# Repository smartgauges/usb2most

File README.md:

# usb2most
USB to MOST adapter to translate audio from a USB([UAC1](https://en.wikipedia.org/wiki/USB#Audio_streaming)) to MOST([Media Oriented Systems Transport](https://en.wikipedia.org/wiki/MOST_Bus)) bus

Interfaces:
- 8 audio channels(16bit/48kHz) over MOST bus
- 2 audio channels(16bit/48kHz) over USB
- 4 CAN for HS/HS" and MS/MS"
- 1 LIN for analogue watch
- 1 UART for CANBUS emulation

[More info](https://www.drive2.ru/l/524415370476389031/)

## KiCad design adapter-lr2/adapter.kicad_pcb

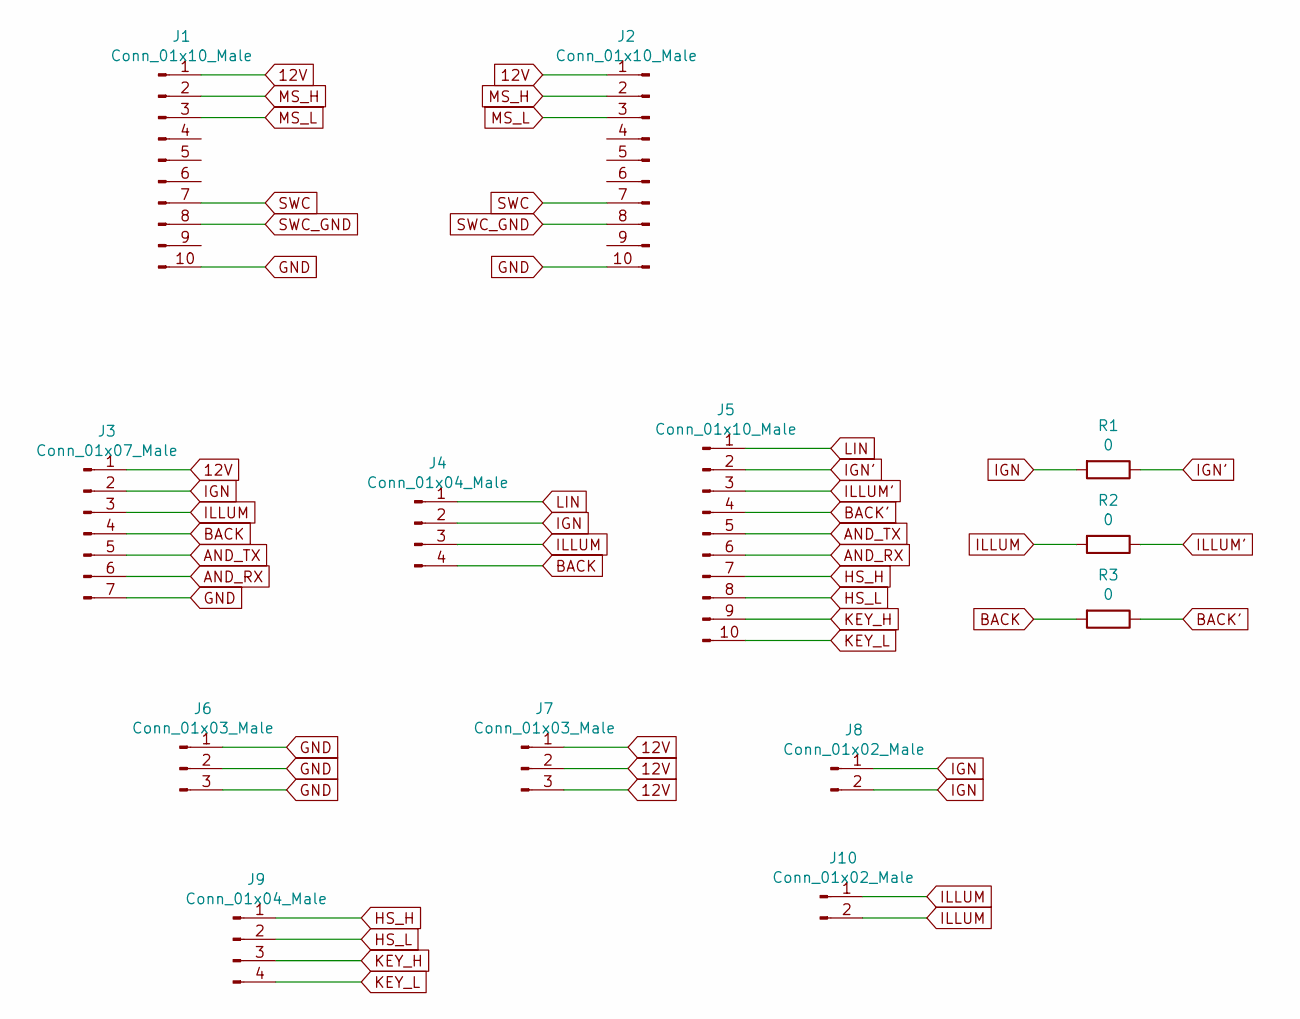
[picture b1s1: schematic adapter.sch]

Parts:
J1: Conn_01x10_Male; IL-AG5-10P-S3L2
J2, J5: Conn_01x10_Male; PinHeader_1x10_P2.54mm_Vertical
J3: Conn_01x07_Male; PinHeader_1x07_P2.54mm_Vertical
J4, J9: Conn_01x04_Male; PinHeader_1x04_P2.54mm_Vertical
J6, J7: Conn_01x03_Male; PinHeader_1x03_P2.54mm_Vertical
J8, J10: Conn_01x02_Male; PinHeader_1x02_P2.54mm_Vertical
R1, R2, R3: 0; R_0805_2012Metric

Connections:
12V: J1.1, J2.1, J3.1, J7.1, J7.2, J7.3
AND_RX: J3.6, J5.6
AND_TX: J3.5, J5.5
BACK: J3.4, J4.4, R3.2
BACK': J5.4, R3.1
GND: J1.10, J2.10, J3.7, J6.1, J6.2, J6.3
HS_H: J5.7, J9.1
HS_L: J5.8, J9.2
IGN: J3.2, J4.2, J8.1, J8.2, R1.2
IGN': J5.2, R1.1
ILLUM: J3.3, J4.3, J10.1, J10.2, R2.2
ILLUM': J5.3, R2.1
KEY_H: J5.9, J9.3
KEY_L: J5.10, J9.4
LIN: J4.1, J5.1
MS_H: J1.2, J2.2
MS_L: J1.3, J2.3
SWC: J1.7, J2.7
SWC_GND: J1.8, J2.8

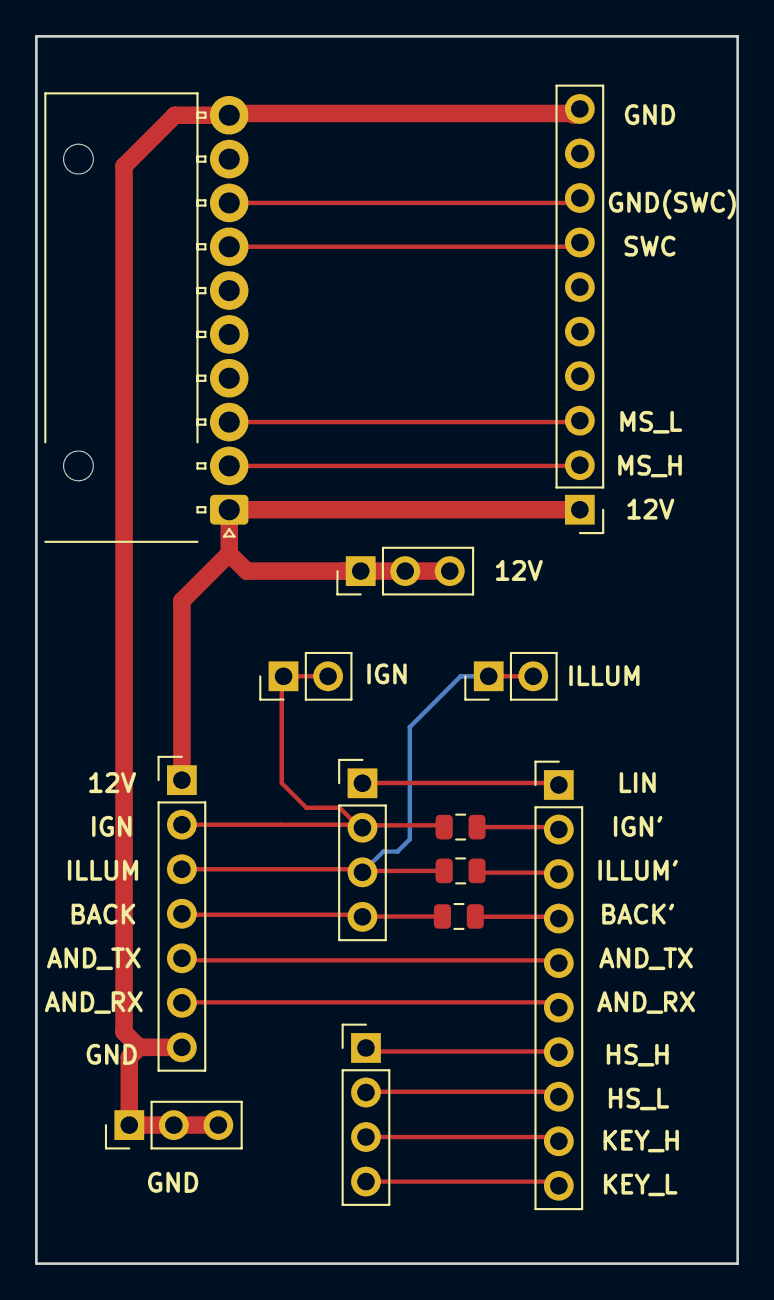
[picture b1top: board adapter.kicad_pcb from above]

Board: 2 copper layers, 40.0 x 70.0 mm, 13 parts (0 on the bottom side), 19 nets.

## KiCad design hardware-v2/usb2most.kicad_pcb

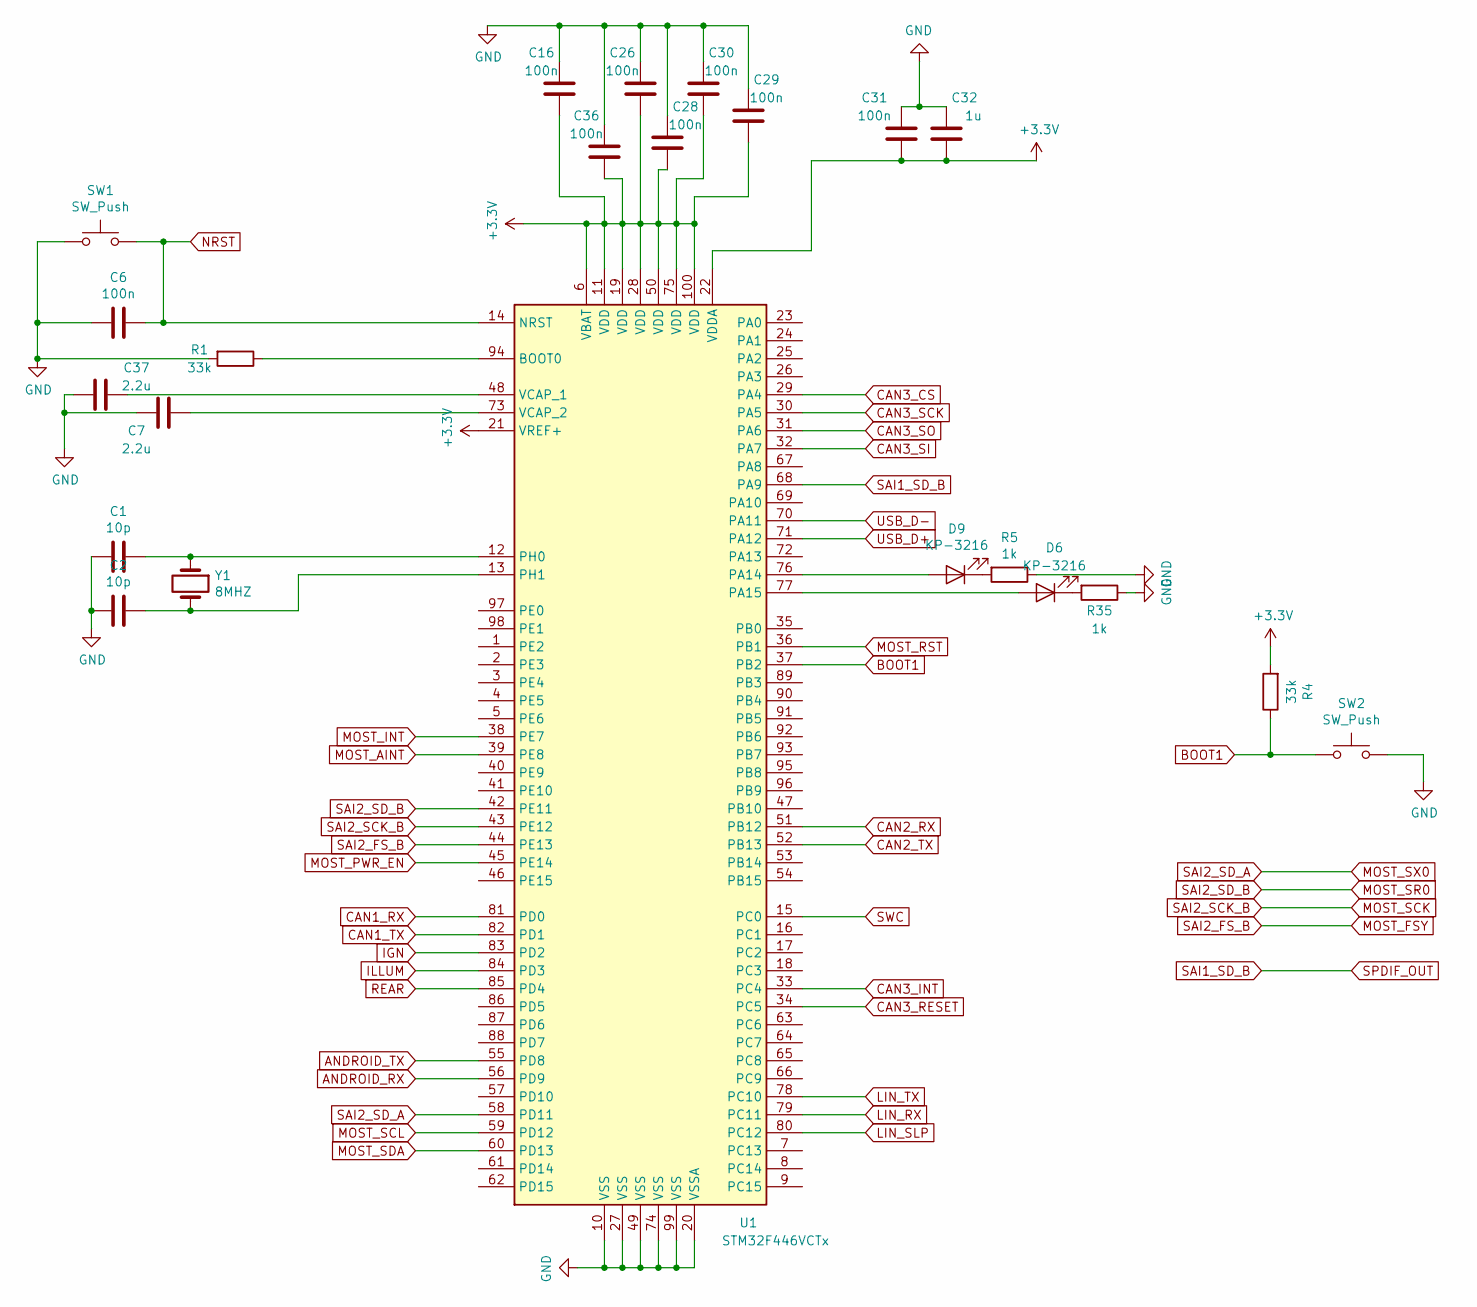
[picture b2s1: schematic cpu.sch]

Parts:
C1, C2: 10p; C_0805_2012Metric
C6, C16, C26, C28, C29, C30, C31, C36: 100n; C_0805_2012Metric
C7, C37: 2.2u; C_1206_3216Metric
C32: 1u; C_1206_3216Metric
D6, D9: KP-3216; R_1206_3216Metric
R1, R4: 33k; R_0805_2012Metric
R5, R35: 1k; R_0805_2012Metric
SW1, SW2: SW_Push; SW_SPST_EVQPE1
U1: STM32F446VCTx; LQFP-100_14x14mm_P0.5mm
Y1: 8MHZ; Crystal_HC49-U_Vertical

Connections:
+3V3: C16.1, C26.1, C28.1, C29.1, C30.1, C31.1, C32.1, C36.1, R4.2, U1.6 (VBAT), U1.11 (VDD), U1.19 (VDD), U1.21 (VREF+), U1.22 (VDDA), U1.28 (VDD), U1.50 (VDD), U1.75 (VDD), U1.100 (VDD); also elsewhere on the board
ANDROID_RX: U1.56 (PD9); also elsewhere on the board
ANDROID_TX: U1.55 (PD8); also elsewhere on the board
BOOT1: R4.1, SW2.1, U1.37 (PB2)
CAN1_RX: U1.81 (PD0); also elsewhere on the board
CAN1_TX: U1.82 (PD1); also elsewhere on the board
CAN2_RX: U1.51 (PB12); also elsewhere on the board
CAN2_TX: U1.52 (PB13); also elsewhere on the board
CAN3_CS: U1.29 (PA4); also elsewhere on the board
CAN3_INT: U1.33 (PC4); also elsewhere on the board
CAN3_RESET: U1.34 (PC5); also elsewhere on the board
CAN3_SCK: U1.30 (PA5); also elsewhere on the board
CAN3_SI: U1.32 (PA7); also elsewhere on the board
CAN3_SO: U1.31 (PA6); also elsewhere on the board
GND: C1.2, C2.2, C6.2, C7.2, C16.2, C26.2, C28.2, C29.2, C30.2, C31.2, C32.2, C36.2, C37.2, R1.2, R5.1, R35.1, SW1.1, SW2.2, U1.10 (VSS), U1.20 (VSSA), U1.27 (VSS), U1.49 (VSS), U1.74 (VSS), U1.99 (VSS); also elsewhere on the board
IGN: U1.83 (PD2); also elsewhere on the board
ILLUM: U1.84 (PD3); also elsewhere on the board
LIN_RX: U1.79 (PC11); also elsewhere on the board
LIN_SLP: U1.80 (PC12); also elsewhere on the board
LIN_TX: U1.78 (PC10); also elsewhere on the board
MOST_AINT: U1.39 (PE8); also elsewhere on the board
MOST_FSY: U1.44 (PE13); also elsewhere on the board
MOST_INT: U1.38 (PE7); also elsewhere on the board
MOST_PWR_EN: U1.45 (PE14); also elsewhere on the board
MOST_RST: U1.36 (PB1); also elsewhere on the board
MOST_SCK: U1.43 (PE12); also elsewhere on the board
MOST_SCL: U1.59 (PD12); also elsewhere on the board
MOST_SDA: U1.60 (PD13); also elsewhere on the board
MOST_SR0: U1.42 (PE11); also elsewhere on the board
MOST_SX0: U1.58 (PD11); also elsewhere on the board
NRST: C6.1, SW1.2, U1.14 (NRST)
unnamed: C1.1, U1.12 (PH0), Y1.1
unnamed: C2.1, U1.13 (PH1), Y1.2
unnamed: C7.1, U1.73 (VCAP_2)
unnamed: C37.1, U1.48 (VCAP_1)
unnamed: D6.1 (K), R35.2
unnamed: D6.2 (A), U1.77 (PA15)
unnamed: D9.1 (K), R5.2
unnamed: D9.2 (A), U1.76 (PA14)
unnamed: R1.1, U1.94 (BOOT0)
REAR: U1.85 (PD4); also elsewhere on the board
SAI1_SD_B: U1.68 (PA9); also elsewhere on the board
SWC: U1.15 (PC0); also elsewhere on the board
USB_D+: U1.71 (PA12); also elsewhere on the board
USB_D-: U1.70 (PA11); also elsewhere on the board

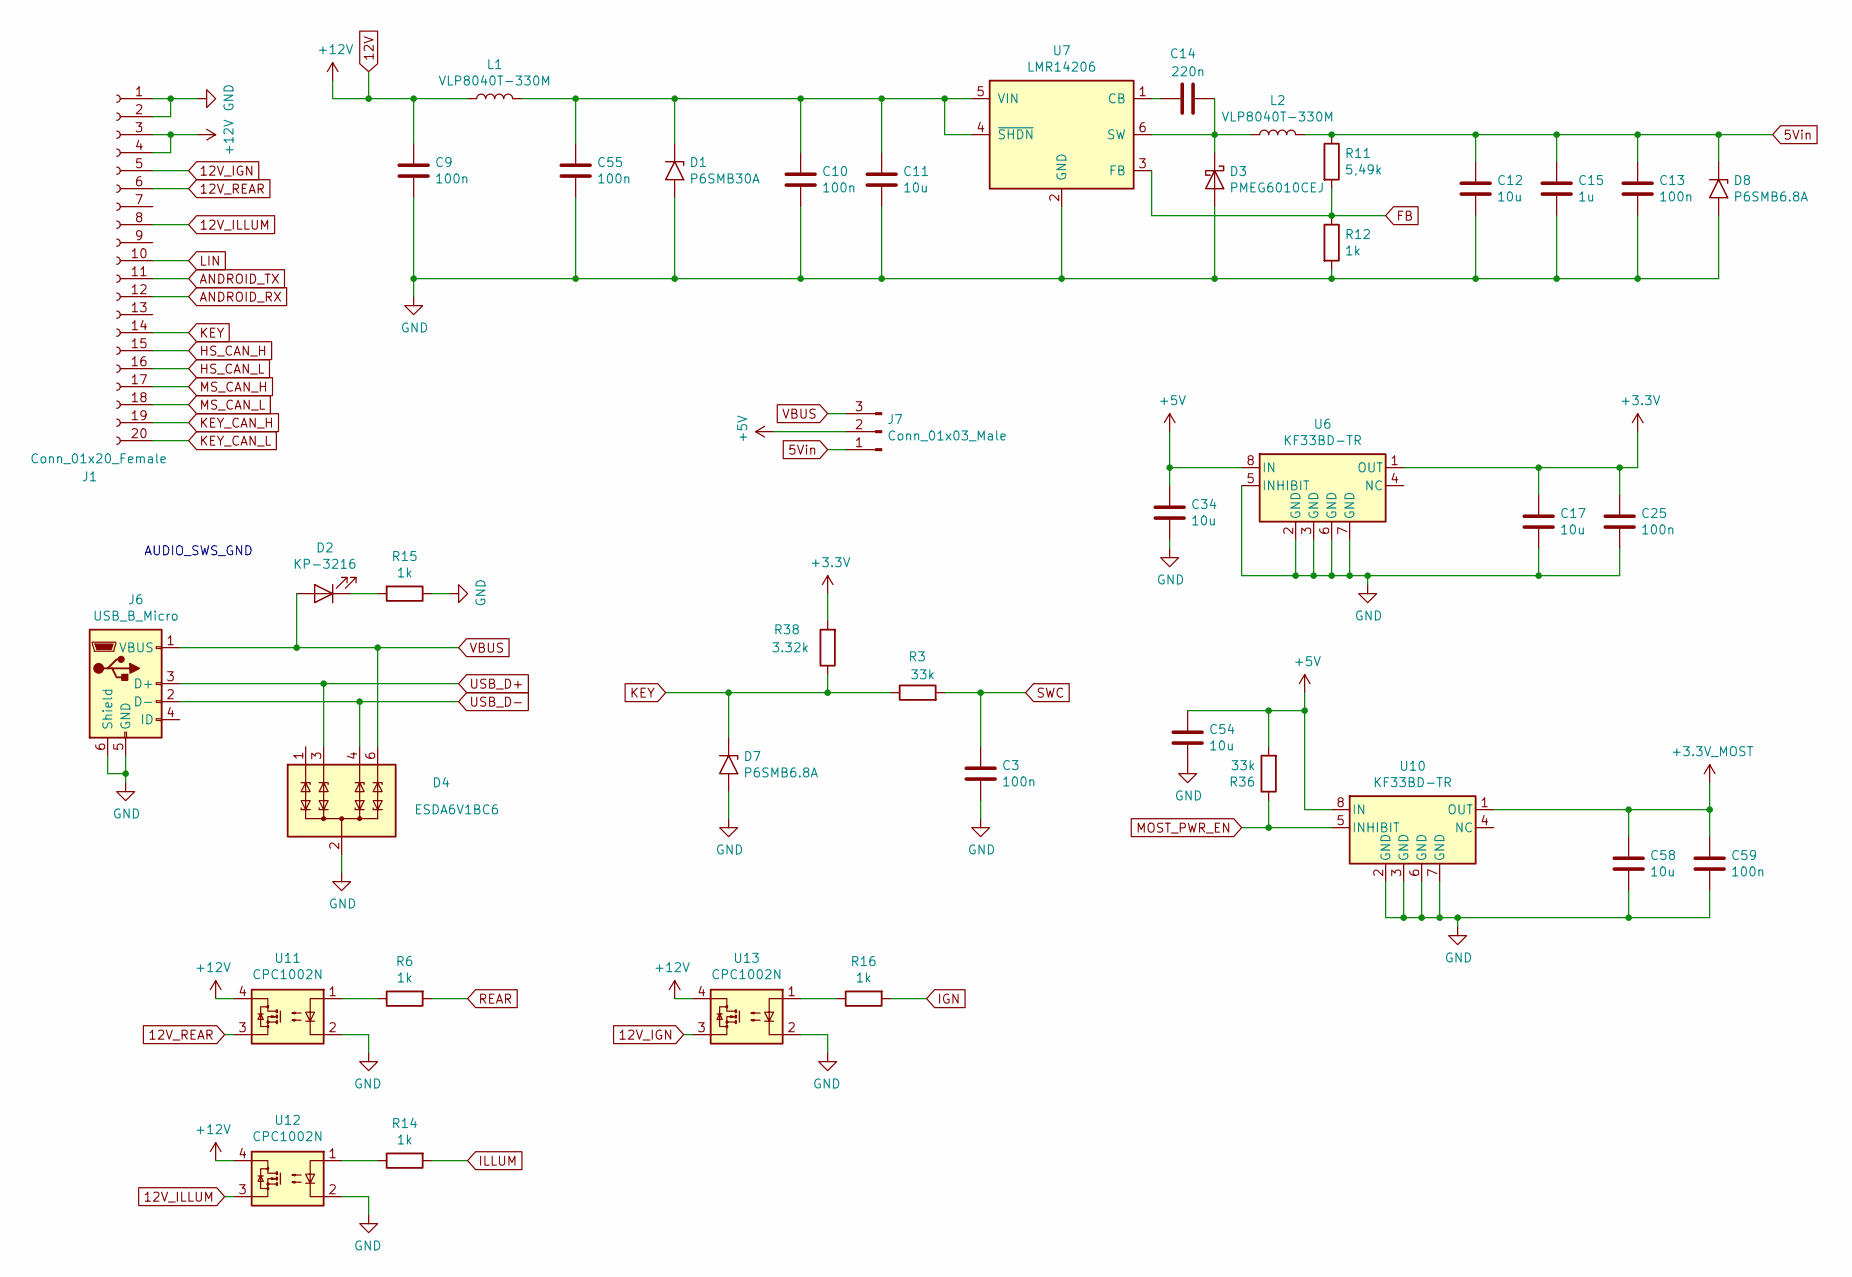
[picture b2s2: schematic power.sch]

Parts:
C3: 100n; C_1206_3216Metric
C9, C10, C13, C25, C55, C59: 100n; C_0805_2012Metric
C11, C12: 10u; C_1812_4532Metric
C14: 220n; C_0805_2012Metric
C15: 1u; C_1206_3216Metric
C17, C34, C54, C58: 10u; C_1206_3216Metric
D1: P6SMB30A; D_SMB
D2: KP-3216; R_1206_3216Metric
D3: PMEG6010CEJ; D_SOD-323
D4: ESDA6V1BC6; SOT-23-6
D7, D8: P6SMB6.8A; D_SMB
J1: Conn_01x20_Female; PinHeader_2x10_P2.00mm_Vertical
J6: USB_B_Micro; USB_Micro-B_Molex-105017-0001
J7: Conn_01x03_Male; PinSocket_1x03_P2.54mm_Vertical
L1, L2: VLP8040T-330M; L_TDK_VLP8040
R3, R36: 33k; R_0805_2012Metric
R6, R12, R14, R15, R16: 1k; R_0805_2012Metric
R11: 5,49k; R_0805_2012Metric
R38: 3.32k; R_0805_2012Metric
U6, U10: KF33BD-TR; SO-8_3.9x4.9mm_P1.27mm
U7: LMR14206; SOT-23-6_Handsoldering
U11, U12, U13: CPC1002N; SOP-4_3.8x4.1mm_P2.54mm

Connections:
5Vin: C12.1, C13.1, C15.1, D8.1 (A1), J7.1, L2.2, R11.1
12V: C9.1, J1.3, J1.4, L1.1, U11.4, U12.4, U13.4; also elsewhere on the board
12V_IGN: J1.5, U13.3
12V_ILLUM: J1.8, U12.3
12V_REAR: J1.6, U11.3
+3.3_MOST: C58.1, C59.1, U10.1 (OUT); also elsewhere on the board
+3V3: C17.1, C25.1, R38.2, U6.1 (OUT); also elsewhere on the board
+5V: C34.1, C54.1, J7.2, R36.2, U6.8 (IN), U10.8 (IN); also elsewhere on the board
ANDROID_RX: J1.12; also elsewhere on the board
ANDROID_TX: J1.11; also elsewhere on the board
FB: R11.2, R12.1, U7.3 (FB)
GND: C3.2, C9.2, C10.2, C11.2, C12.2, C13.2, C15.2, C17.2, C25.2, C34.2, C54.2, C55.2, C58.2, C59.2, D1.2 (A2), D3.2 (A), D4.2 (COM), D4.5 (COM), D7.2 (A2), D8.2 (A2), J1.1, J1.2, J6.5 (GND), J6.6 (Shield), R12.2, R15.1, U6.2 (GND), U6.3 (GND), U6.5 (INHIBIT), U6.6 (GND), U6.7 (GND), U7.2 (GND), U10.2 (GND), U10.3 (GND), U10.6 (GND), U10.7 (GND), U11.2, U12.2, U13.2; also elsewhere on the board
HS_CAN_H: J1.15; also elsewhere on the board
HS_CAN_L: J1.16; also elsewhere on the board
IGN: R16.2; also elsewhere on the board
ILLUM: R14.2; also elsewhere on the board
KEY: D7.1 (A1), J1.14, R3.1, R38.1
KEY_CAN_H: J1.19; also elsewhere on the board
KEY_CAN_L: J1.20; also elsewhere on the board
LIN: J1.10; also elsewhere on the board
MOST_PWR_EN: R36.1, U10.5 (INHIBIT); also elsewhere on the board
MS_CAN_H: J1.17; also elsewhere on the board
MS_CAN_L: J1.18; also elsewhere on the board
unnamed: C10.1, C11.1, C55.1, D1.1 (A1), L1.2, U7.4 (~SHDN), U7.5 (VIN)
unnamed: C14.1, U7.1 (CB)
unnamed: C14.2, D3.1 (K), L2.1, U7.6 (SW)
unnamed: D2.1 (K), R15.2
unnamed: R6.1, U11.1
unnamed: R14.1, U12.1
unnamed: R16.1, U13.1
REAR: R6.2; also elsewhere on the board
SWC: C3.1, R3.2; also elsewhere on the board
USB_D+: D4.3 (TVS2), J6.3 (D+); also elsewhere on the board
USB_D-: D4.4 (TVS3), J6.2 (D-); also elsewhere on the board
VBUS: D2.2 (A), D4.6 (TVS4), J6.1 (VBUS), J7.3

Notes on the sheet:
AUDIO_SWS_GND

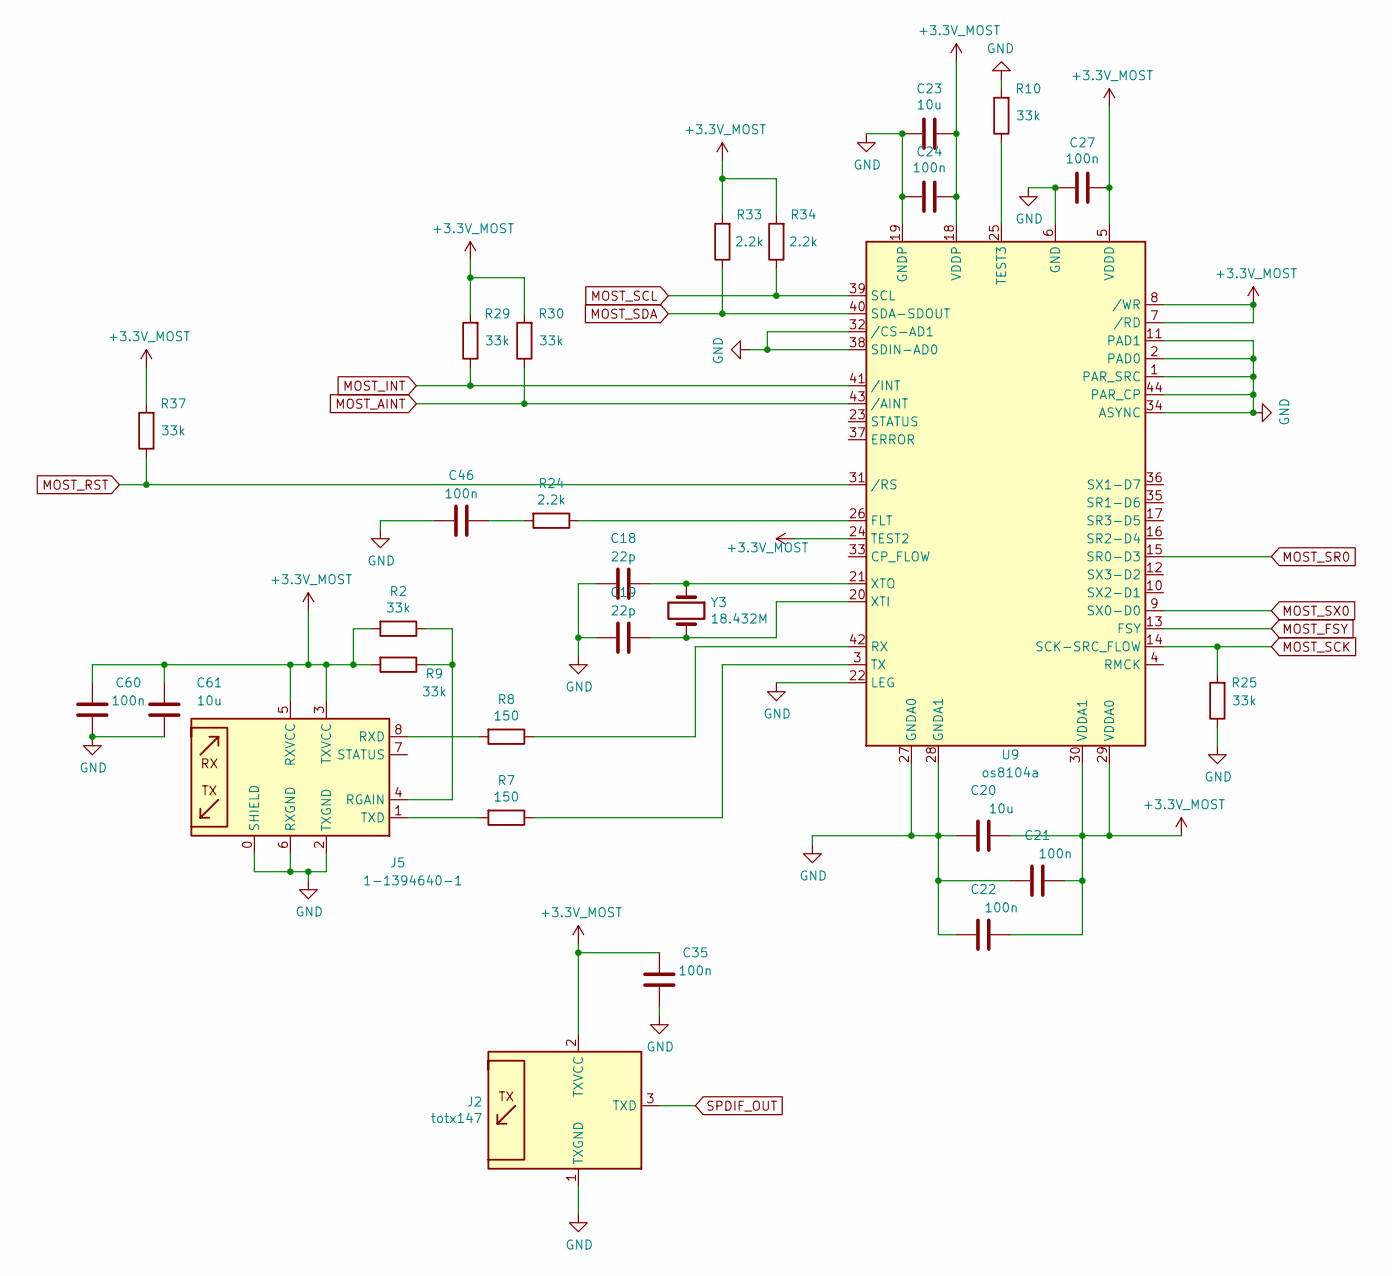
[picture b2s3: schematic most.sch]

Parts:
C18, C19: 22p; C_0805_2012Metric
C20, C23, C61: 10u; C_1206_3216Metric
C21, C22, C24, C27, C35, C46, C60: 100n; C_0805_2012Metric
J2: totx147; TOTX147
J5: 1-1394640-1; TYCO_1_1394640_1
R2, R9, R10, R25, R29, R30, R37: 33k; R_0805_2012Metric
R7, R8: 150; R_0805_2012Metric
R24, R33, R34: 2.2k; R_0805_2012Metric
U9: os8104a; LQFP-44_10x10mm_P0.8mm
Y3: 18.432M; Crystal_HC49-U_Vertical

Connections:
+3.3_MOST: C20.1, C21.1, C22.1, C23.1, C24.1, C27.1, C35.2, C60.2, C61.2, J2.2 (TXVCC), J5.3 (TXVCC), J5.5 (RXVCC), R2.2, R9.2, R29.2, R30.2, R33.2, R34.2, R37.2, U9.5 (VDDD), U9.7 (/RD), U9.8 (/WR), U9.18 (VDDP), U9.24 (TEST2), U9.29 (VDDA0), U9.30 (VDDA1); also elsewhere on the board
GND: C18.2, C19.2, C20.2, C21.2, C22.2, C23.2, C24.2, C27.2, C35.1, C46.2, C60.1, C61.1, J2.1 (TXGND), J5.0 (SHIELD), J5.2 (TXGND), J5.6 (RXGND), R10.2, R25.1, U9.1 (PAR_SRC), U9.2 (PAD0), U9.6 (GND), U9.11 (PAD1), U9.19 (GNDP), U9.22 (LEG), U9.27 (GNDA0), U9.28 (GNDA1), U9.32 (/CS-AD1), U9.34 (ASYNC), U9.38 (SDIN-AD0), U9.44 (PAR_CP); also elsewhere on the board
MOST_AINT: R30.1, U9.43 (/AINT); also elsewhere on the board
MOST_FSY: U9.13 (FSY); also elsewhere on the board
MOST_INT: R29.1, U9.41 (/INT); also elsewhere on the board
MOST_RST: R37.1, U9.31 (/RS); also elsewhere on the board
MOST_SCK: R25.2, U9.14 (SCK-SRC_FLOW); also elsewhere on the board
MOST_SCL: R34.1, U9.39 (SCL); also elsewhere on the board
MOST_SDA: R33.1, U9.40 (SDA-SDOUT); also elsewhere on the board
MOST_SR0: U9.15 (SR0-D3); also elsewhere on the board
MOST_SX0: U9.9 (SX0-D0); also elsewhere on the board
unnamed: C18.1, U9.21 (XTO), Y3.1
unnamed: C19.1, U9.20 (XTI), Y3.2
unnamed: C46.1, R24.2
unnamed: J5.1 (TXD), R7.2
unnamed: J5.4 (RGAIN), R2.1, R9.1
unnamed: J5.8 (RXD), R8.2
unnamed: R7.1, U9.3 (TX)
unnamed: R8.1, U9.42 (RX)
unnamed: R10.1, U9.25 (TEST3)
unnamed: R24.1, U9.26 (FLT)
SAI1_SD_B: J2.3 (TXD); also elsewhere on the board

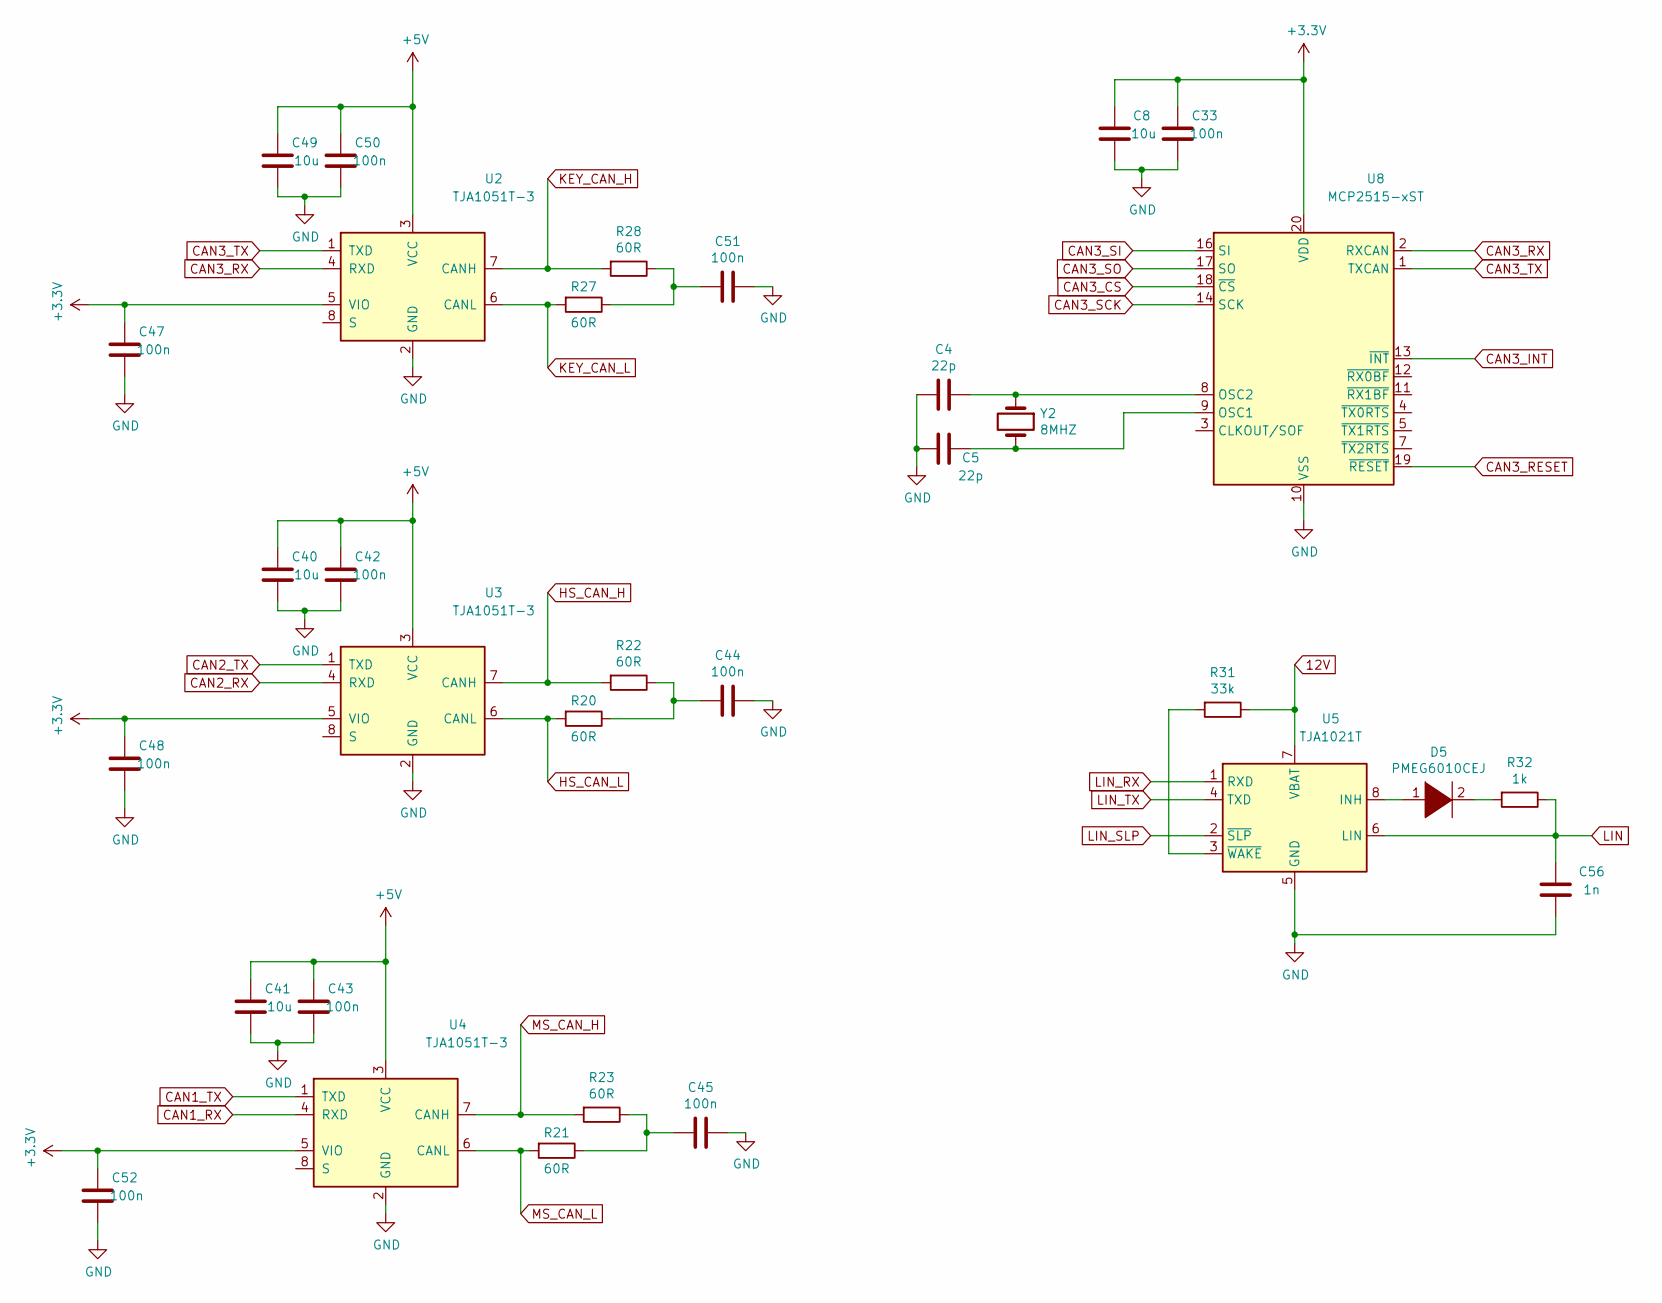
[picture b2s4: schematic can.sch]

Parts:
C4, C5: 22p; C_0805_2012Metric
C8, C40, C41, C49: 10u; C_1206_3216Metric
C33, C42, C43, C44, C45, C47, C48, C50, C51, C52: 100n; C_0805_2012Metric
C56: 1n; C_0805_2012Metric
D5: PMEG6010CEJ; R_0805_2012Metric
R20, R21, R22, R23, R27, R28: 60R; R_0805_2012Metric
R31: 33k; R_0805_2012Metric
R32: 1k; R_0805_2012Metric
U2, U3, U4: TJA1051T-3; SOIC-8_3.9x4.9mm_P1.27mm
U5: TJA1021T; SOIC-8_3.9x4.9mm_P1.27mm
U8: MCP2515-xST; TSSOP-20_4.4x6.5mm_P0.65mm
Y2: 8MHZ; Crystal_HC49-U_Vertical

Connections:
12V: R31.1, U5.7 (VBAT); also elsewhere on the board
+3V3: C8.2, C33.2, C47.2, C48.2, C52.2, U2.5 (VIO), U3.5 (VIO), U4.5 (VIO), U8.20 (VDD); also elsewhere on the board
+5V: C40.2, C41.2, C42.2, C43.2, C49.2, C50.2, U2.3 (VCC), U3.3 (VCC), U4.3 (VCC); also elsewhere on the board
CAN1_RX: U4.4 (RXD); also elsewhere on the board
CAN1_TX: U4.1 (TXD); also elsewhere on the board
CAN2_RX: U3.4 (RXD); also elsewhere on the board
CAN2_TX: U3.1 (TXD); also elsewhere on the board
CAN3_CS: U8.18 (~CS); also elsewhere on the board
CAN3_INT: U8.13 (~INT); also elsewhere on the board
CAN3_RESET: U8.19 (~RESET); also elsewhere on the board
CAN3_RX: U2.4 (RXD), U8.2 (RXCAN)
CAN3_SCK: U8.14 (SCK); also elsewhere on the board
CAN3_SI: U8.16 (SI); also elsewhere on the board
CAN3_SO: U8.17 (SO); also elsewhere on the board
CAN3_TX: U2.1 (TXD), U8.1 (TXCAN)
GND: C4.2, C5.2, C8.1, C33.1, C40.1, C41.1, C42.1, C43.1, C44.1, C45.1, C47.1, C48.1, C49.1, C50.1, C51.1, C52.1, C56.1, U2.2 (GND), U3.2 (GND), U4.2 (GND), U5.5 (GND), U8.10 (VSS); also elsewhere on the board
HS_CAN_H: R22.2, U3.7 (CANH); also elsewhere on the board
HS_CAN_L: R20.2, U3.6 (CANL); also elsewhere on the board
KEY_CAN_H: R28.2, U2.7 (CANH); also elsewhere on the board
KEY_CAN_L: R27.2, U2.6 (CANL); also elsewhere on the board
LIN: C56.2, R32.1, U5.6 (LIN); also elsewhere on the board
LIN_RX: U5.1 (RXD); also elsewhere on the board
LIN_SLP: U5.2 (~SLP~); also elsewhere on the board
LIN_TX: U5.4 (TXD); also elsewhere on the board
MS_CAN_H: R23.2, U4.7 (CANH); also elsewhere on the board
MS_CAN_L: R21.2, U4.6 (CANL); also elsewhere on the board
unnamed: C4.1, U8.8 (OSC2), Y2.1
unnamed: C5.1, U8.9 (OSC1), Y2.2
unnamed: C44.2, R20.1, R22.1
unnamed: C45.2, R21.1, R23.1
unnamed: C51.2, R27.1, R28.1
unnamed: D5.1 (K), U5.8 (INH)
unnamed: D5.2 (A), R32.2
unnamed: R31.2, U5.3 (~WAKE~)

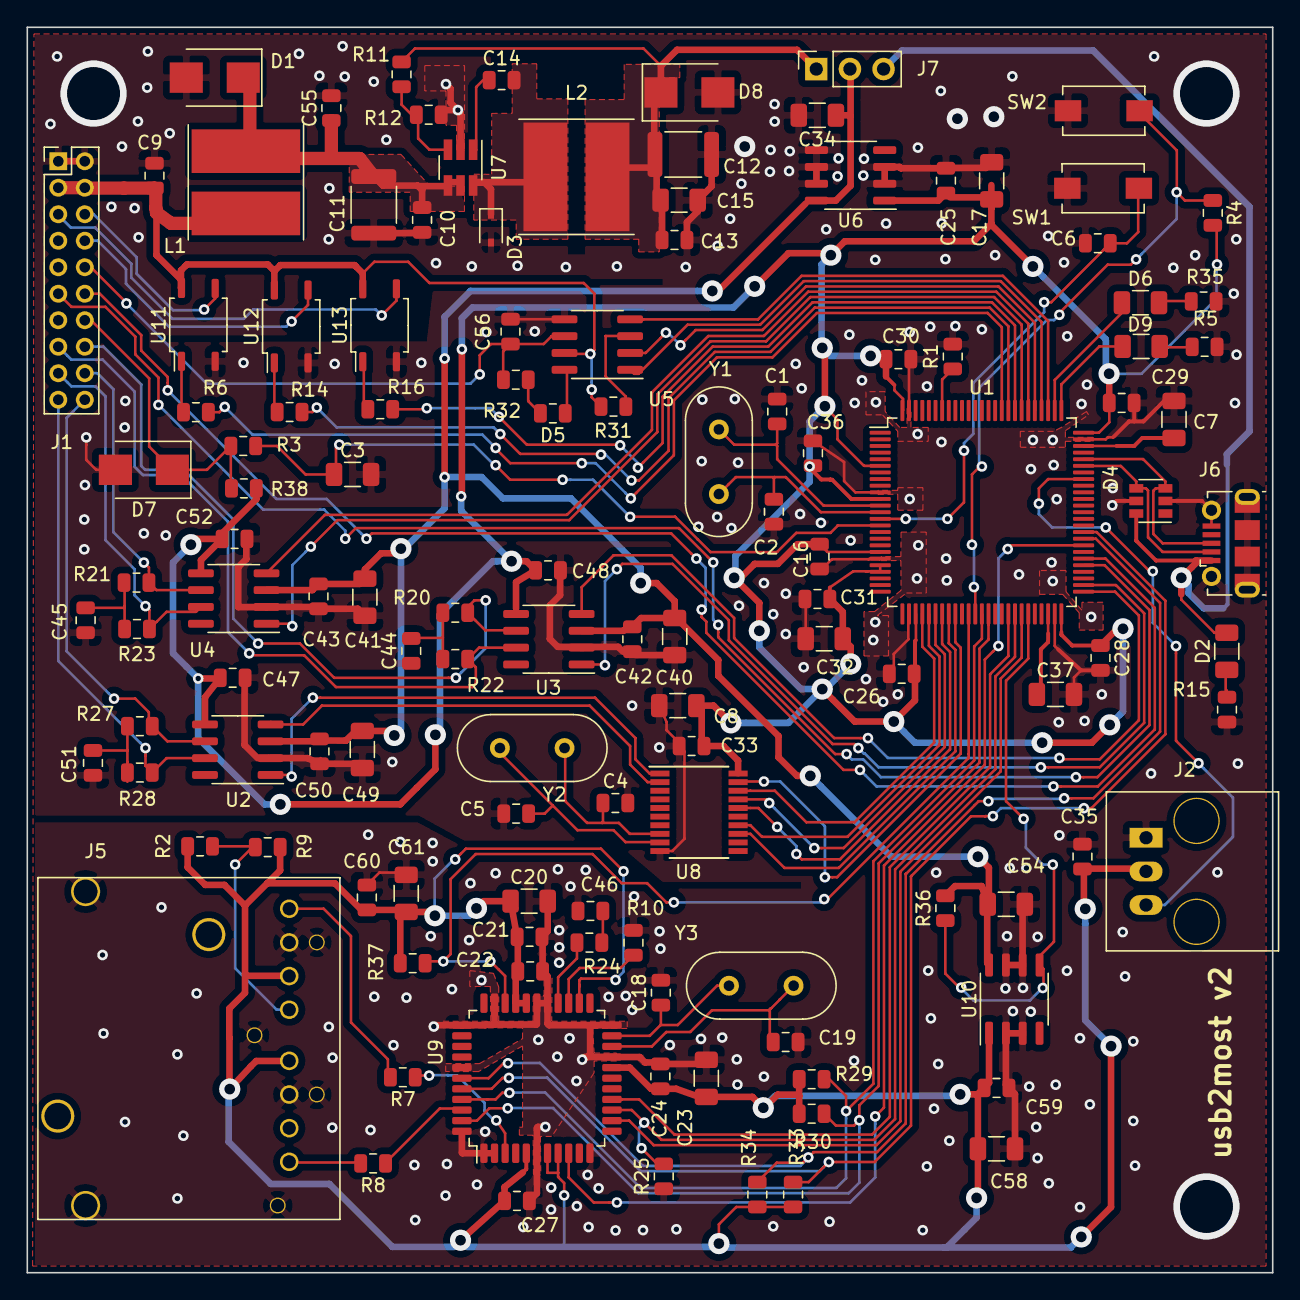
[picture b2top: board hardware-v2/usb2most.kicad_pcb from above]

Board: 2 copper layers, 94.0 x 94.0 mm, 124 parts (0 on the bottom side), 89 nets.
